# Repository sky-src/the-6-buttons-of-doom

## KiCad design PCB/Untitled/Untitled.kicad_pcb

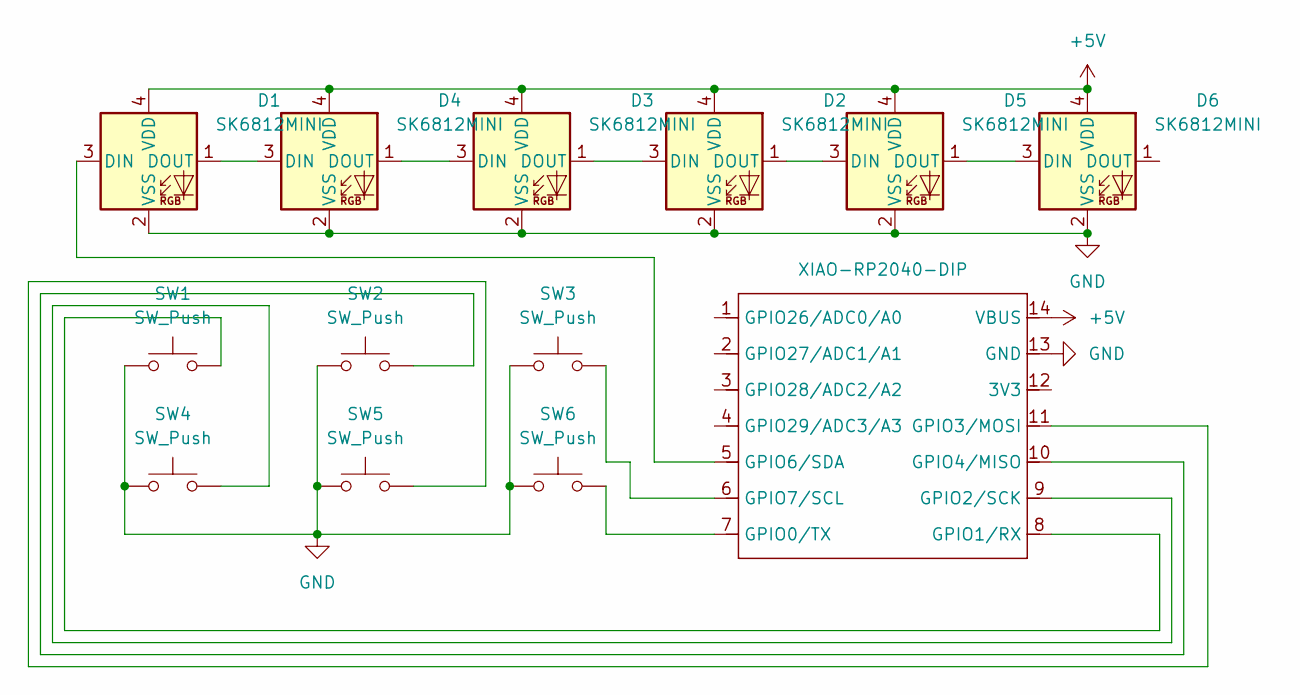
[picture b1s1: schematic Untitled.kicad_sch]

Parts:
D1, D2, D3, D4, D5, D6: SK6812MINI; LED_SK6812MINI_PLCC4_3.5x3.5mm_P1.75mm
SW1, SW2, SW3, SW4, SW5, SW6: SW_Push; SW_Cherry_MX_1.00u_PCB
U2: XIAO-RP2040-DIP

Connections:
+5V: D1.4 (VDD), D2.4 (VDD), D3.4 (VDD), D4.4 (VDD), D5.4 (VDD), D6.4 (VDD), U2.14 (VBUS)
GND: D1.2 (VSS), D2.2 (VSS), D3.2 (VSS), D4.2 (VSS), D5.2 (VSS), D6.2 (VSS), SW1.1, SW2.1, SW3.1, SW4.1, SW5.1, SW6.1, U2.13 (GND)
unnamed: D1.3 (DIN), U2.5 (GPIO6/SDA)
unnamed: D1.1 (DOUT), D4.3 (DIN)
unnamed: D2.3 (DIN), D3.1 (DOUT)
unnamed: D2.1 (DOUT), D5.3 (DIN)
unnamed: D3.3 (DIN), D4.1 (DOUT)
unnamed: D5.1 (DOUT), D6.3 (DIN)
unnamed: SW6.2, U2.7 (GPIO0/TX)
unnamed: SW1.2, U2.8 (GPIO1/RX)
unnamed: SW4.2, U2.9 (GPIO2/SCK)
unnamed: SW5.2, U2.11 (GPIO3/MOSI)
unnamed: SW2.2, U2.10 (GPIO4/MISO)
unnamed: SW3.2, U2.6 (GPIO7/SCL)

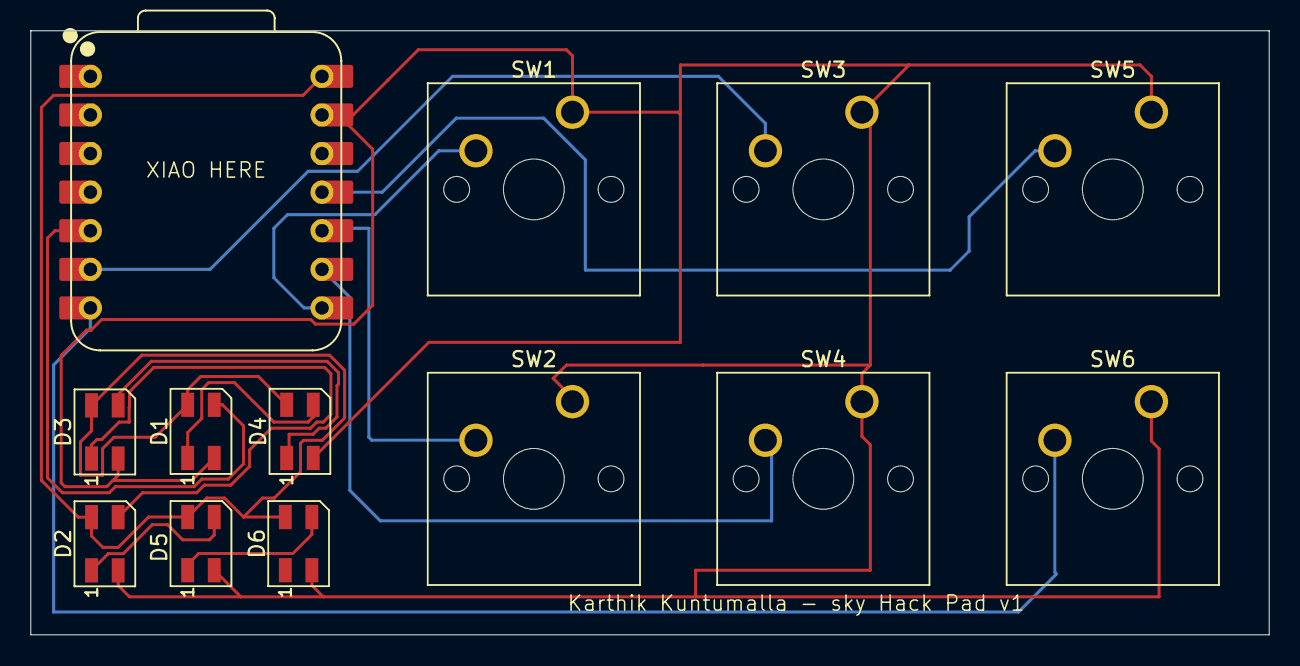
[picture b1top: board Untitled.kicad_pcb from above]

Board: 2 copper layers, 81.5 x 39.8 mm, 13 parts (0 on the bottom side), 14 nets.

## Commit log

2026-03-18 Add local project files to github
2026-03-18 Keyboard firmware push
